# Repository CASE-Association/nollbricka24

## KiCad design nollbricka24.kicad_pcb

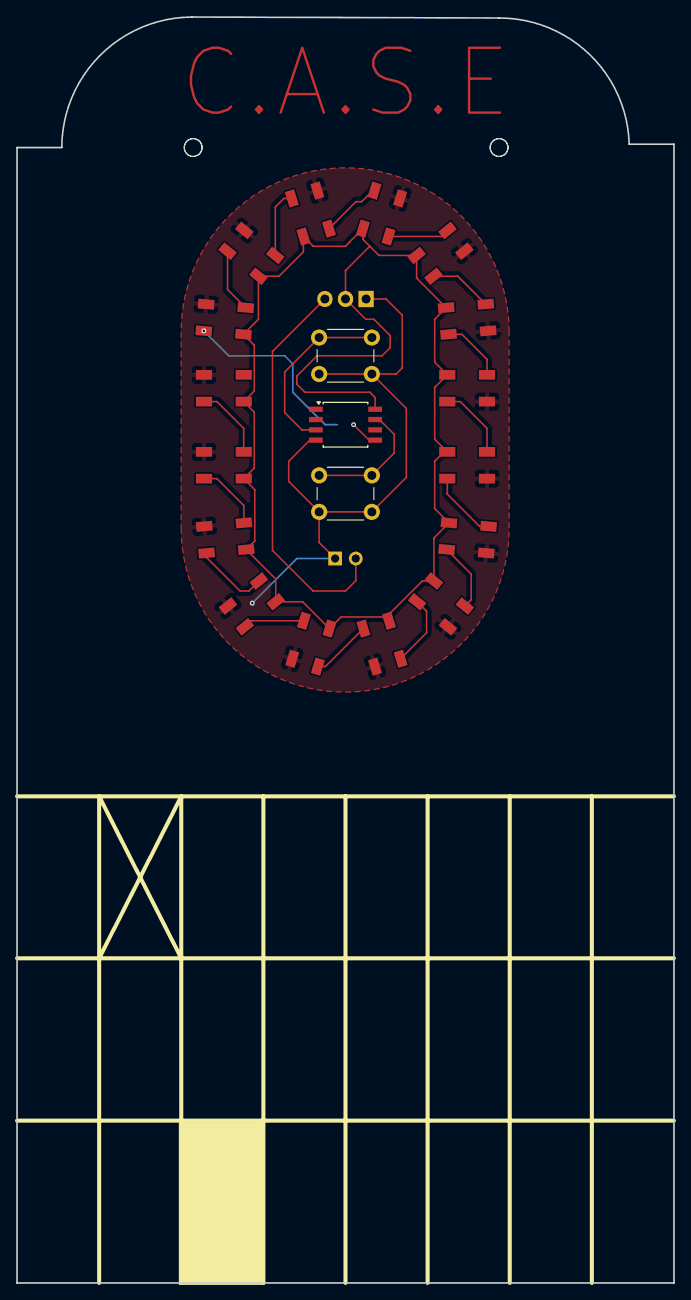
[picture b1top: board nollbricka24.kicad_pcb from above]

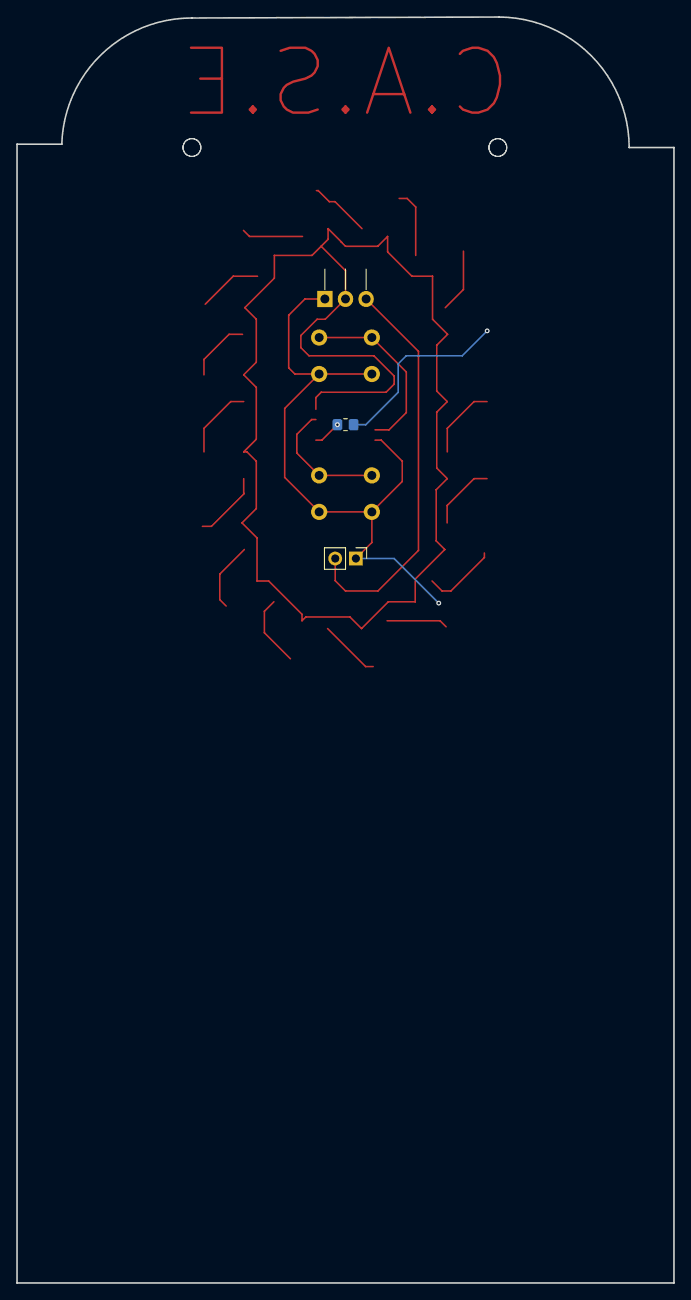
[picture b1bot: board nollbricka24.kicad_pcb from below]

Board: 2 copper layers, 81.0 x 156.1 mm, 22 parts (3 on the bottom side), 22 nets.

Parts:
D1, D2, D3, D4, D5, D6, D7, D8, D9, D10, D11, D12, D13, D14, D15, D16: WS2812B; LED_WS2812B_PLCC4_5.0x5.0mm_P3.2mm_modified
J1: PINHD-1X2; PinHeader_1x02_P2.54mm_Vertical
R1: 330; R_0805_2012Metric_Pad1.20x1.40mm_HandSolder
SW1, SW2: SW_Push_Dual; SW_PUSH_6mm_H5mm
U1: ATtiny85-20S; SOIC-8W_5.3x5.3mm_P1.27mm
VR1: LD1117V50; TO-220-3_Horizontal_TabDown

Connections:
GND: D1.3 (VSS), D2.3 (VSS), D3.3 (VSS), D4.3 (VSS), D5.3 (VSS), D6.3 (VSS), D7.3 (VSS), D8.3 (VSS), D9.3 (VSS), D10.3 (VSS), D11.3 (VSS), D12.3 (VSS), D13.3 (VSS), D14.3 (VSS), D15.3 (VSS), D16.3 (VSS), J1.1, SW1.2, SW2.2, U1.4 (GND), VR1.1 (GND)
unnamed: D1.4 (DIN), R1.1
unnamed: D1.2 (DOUT), D2.4 (DIN)
unnamed: D1.1 (VDD), D2.1 (VDD), D3.1 (VDD), D4.1 (VDD), D5.1 (VDD), D6.1 (VDD), D7.1 (VDD), D8.1 (VDD), D9.1 (VDD), D10.1 (VDD), D11.1 (VDD), D12.1 (VDD), D13.1 (VDD), D14.1 (VDD), D15.1 (VDD), D16.1 (VDD), U1.8 (VCC), VR1.2 (Vout)
unnamed: D2.2 (DOUT), D3.4 (DIN)
unnamed: D3.2 (DOUT), D4.4 (DIN)
unnamed: D4.2 (DOUT), D5.4 (DIN)
unnamed: D5.2 (DOUT), D6.4 (DIN)
unnamed: D6.2 (DOUT), D7.4 (DIN)
unnamed: D7.2 (DOUT), D8.4 (DIN)
unnamed: D8.2 (DOUT), D9.4 (DIN)
unnamed: D9.2 (DOUT), D10.4 (DIN)
unnamed: D10.2 (DOUT), D11.4 (DIN)
unnamed: D11.2 (DOUT), D12.4 (DIN)
unnamed: D12.2 (DOUT), D13.4 (DIN)
unnamed: D13.2 (DOUT), D14.4 (DIN)
unnamed: D14.2 (DOUT), D15.4 (DIN)
unnamed: D15.2 (DOUT), D16.4 (DIN)
unnamed: J1.2, VR1.3 (Vin)
unnamed: R1.2, U1.5 (AREF/PB0)
unnamed: SW2.1, U1.7 (PB2)
unnamed: SW1.1, U1.3 (XTAL2/PB4)

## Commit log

2024-06-03 first design
2024-06-04 fixed missing square
2024-06-06 generated fabrication outputs
2025-09-11 Gult blink o annat fint
